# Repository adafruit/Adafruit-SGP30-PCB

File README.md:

## Adafruit SGP30 Air Quality Sensor PCB

<a href="http://www.adafruit.com/products/3709"><br/>
<a href="http://www.adafruit.com/products/3709"><br/>
Click here to purchase one from the Adafruit shop</a>

PCB files for the Adafruit SGP30 Air Quality Sensor. 

Format is EagleCAD schematic and board layout
* https://www.adafruit.com/product/3709

### Description

Breathe easy with the SGP30 Multi-Pixel Gas Sensor, a fully integrated MOX gas sensor. This is a very fine air quality sensor from the sensor experts at Sensirion, with I2C interfacing and fully calibrated output signals with a typical accuracy of 15% within measured values. The SGP combines multiple metal-oxide sensing elements on one chip to provide more detailed air quality signals.

This is a gas sensor that can detect a wide range of Volatile Organic Compounds (VOCs) and H2 and is intended for indoor air quality monitoring. When connected to your microcontroller (running our library code) it will return a Total Volatile Organic Compound (TVOC) reading and an equivalent carbon dioxide reading (eCO2) over I2C.

The SGP30 has a 'standard' hot-plate MOX sensor, as well as a small microcontroller that controls power to the plate, reads the analog voltage, tracks the baseline calibration, calculates TVOC and eCO2 values, and provides an I2C interface to read from. Unlike the CCS811, this sensor does not require I2C clock stretching.

This part will measure eCO2 (equivalent calculated carbon-dioxide) concentration within a range of 400 to 60,000 parts per million (ppm), and TVOC (Total Volatile Organic Compound) concentration within a range of 0 to 60,000 parts per billion (ppb).

Please note, this sensor, like all VOC/gas sensors, has variability and to get precise measurements you will want to calibrate it against known sources! That said, for general environmental sensors, it will give you a good idea of trends and comparison. The SGP30 does have built in calibration capabilities, note that eCO2 is calculated based on H2 concentration, it is not a 'true' CO2 sensor for laboratory use.

Another nice element to this sensor is the ability to set humidity compensation for better accuracy. An external humidity sensor is required and then the RH% is written over I2C to the sensor, so it can better calculate the TVOC/eCO2 values.

Nice sensor right? So we made it easy for you to get right into your next project. The surface-mount sensor is soldered onto a custom made PCB in the STEMMA QT form factor, making them easy to interface with. The STEMMA QT connectors on either side are compatible with the SparkFun Qwiic I2C connectors. This allows you to make solderless connections between your development board and the SGP30 or to chain it with a wide range of other sensors and accessories using a compatible cable.

We’ve of course broken out all the pins to standard headers and added a 1.8V voltage regulator and level shifting so allow you to use it with either 3.3V or 5V systems such as the Raspberry Pi, or Metro M4 or Arduino Uno.

### License

Adafruit invests time and resources providing this open source design, please support Adafruit and open-source hardware by purchasing products from [Adafruit](https://www.adafruit.com)!

Designed by Kevin (KTOWN) Townsend for Adafruit Industries.

Creative Commons Attribution/Share-Alike, all text above must be included in any redistribution. 
See license.txt for additional details.

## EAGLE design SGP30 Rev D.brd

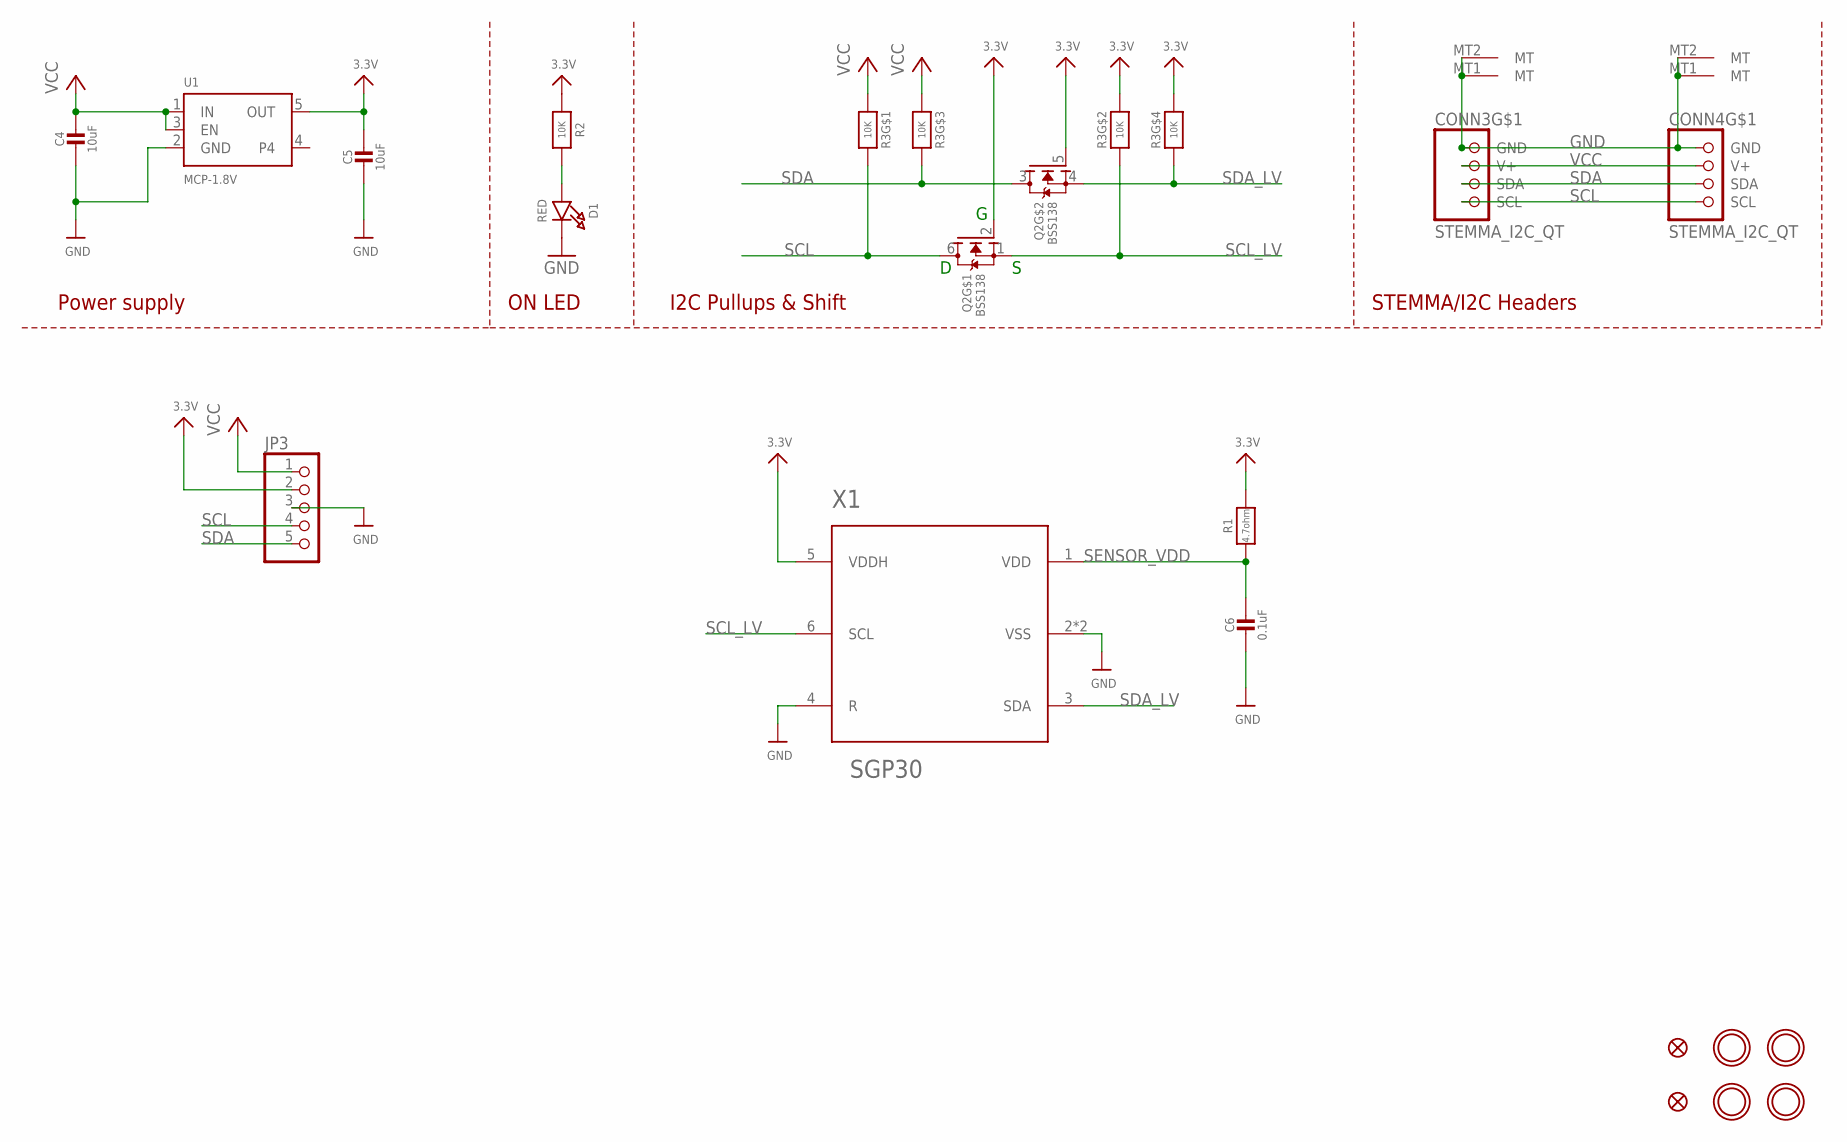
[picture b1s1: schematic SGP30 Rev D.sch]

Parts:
C4, C5: 10uF; 0805-NO
C6: 0.1uF; 0603-NO
CONN3, CONN4: STEMMA_I2C_QT; JST_SH4
D1: RED; CHIPLED_0603_NOOUTLINE
FID3, FID4: FIDUCIAL_1MM
JP3: HEADER-1X570MIL; 1X05_ROUND_70
Q2: BSS138; SOT363
R1: 4.7ohm; 0603-NO
R2: 10K; 0603-NO
R3: 10K; RESPACK_4X0603
U1: MCP-1.8V; SOT23-5
U$28, U$29, U$31, U$32: MOUNTINGHOLE2.5; MOUNTINGHOLE_2.5_PLATED
X1: SGP30

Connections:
3.3V: C5.1, JP3.2, Q2.2 (G), Q2.5 (G), R1.2, R2.1, R3.2 (1), R3.4 (1), U1.5 (OUT), X1.5 (VDDH)
GND: C4.2, C5.2, C6.2, CONN3.1 (GND), CONN3.MT1 (MT), CONN3.MT2 (MT), CONN4.1 (GND), CONN4.MT1 (MT), CONN4.MT2 (MT), D1.C, JP3.3, U1.2 (GND), X1.2 (VSS), X1.4 (R), X1.P$7 (VSS)
unnamed: D1.A, R2.2
SCL: CONN3.4 (SCL), CONN4.4 (SCL), JP3.4, Q2.6 (D), R3.8 (2)
SCL_LV: Q2.1 (S), R3.7 (2), X1.6 (SCL)
SDA: CONN3.3 (SDA), CONN4.3 (SDA), JP3.5, Q2.3 (D), R3.6 (2)
SDA_LV: Q2.4 (S), R3.5 (2), X1.3 (SDA)
SENSOR_VDD: C6.1, R1.1, X1.1 (VDD)
VCC: C4.1, CONN3.2 (V+), CONN4.2 (V+), JP3.1, R3.1, R3.3 (1), U1.1 (IN), U1.3 (EN)

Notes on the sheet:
I2C Pullups & Shift
STEMMA/I2C Headers
ON LED
Power supply

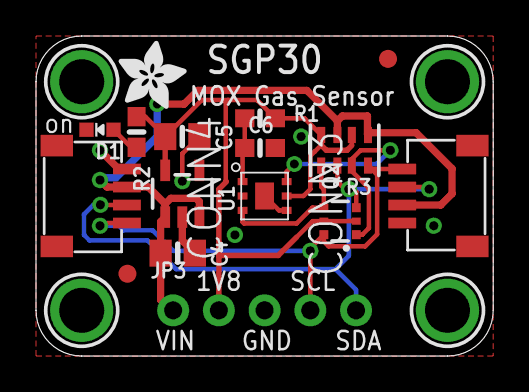
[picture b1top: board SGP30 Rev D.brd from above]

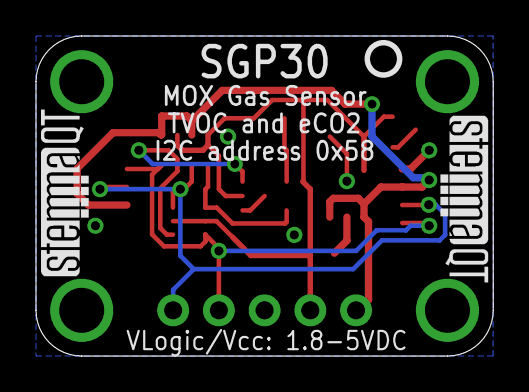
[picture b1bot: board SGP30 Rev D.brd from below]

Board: 2 copper layers, 25.4 x 17.8 mm, 23 parts (3 on the bottom side), 9 nets.

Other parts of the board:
U$34: ADAFRUIT_3.5MM
U$35: PCBFEAT-REV-040
U$36, U$37: STEMMAQT

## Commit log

2020-06-18 Add board files

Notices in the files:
parts and their libraries:
microbuilder: This work is placed in the public domain, and may be freely used for commercial and non-commercial work with the following conditions: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
